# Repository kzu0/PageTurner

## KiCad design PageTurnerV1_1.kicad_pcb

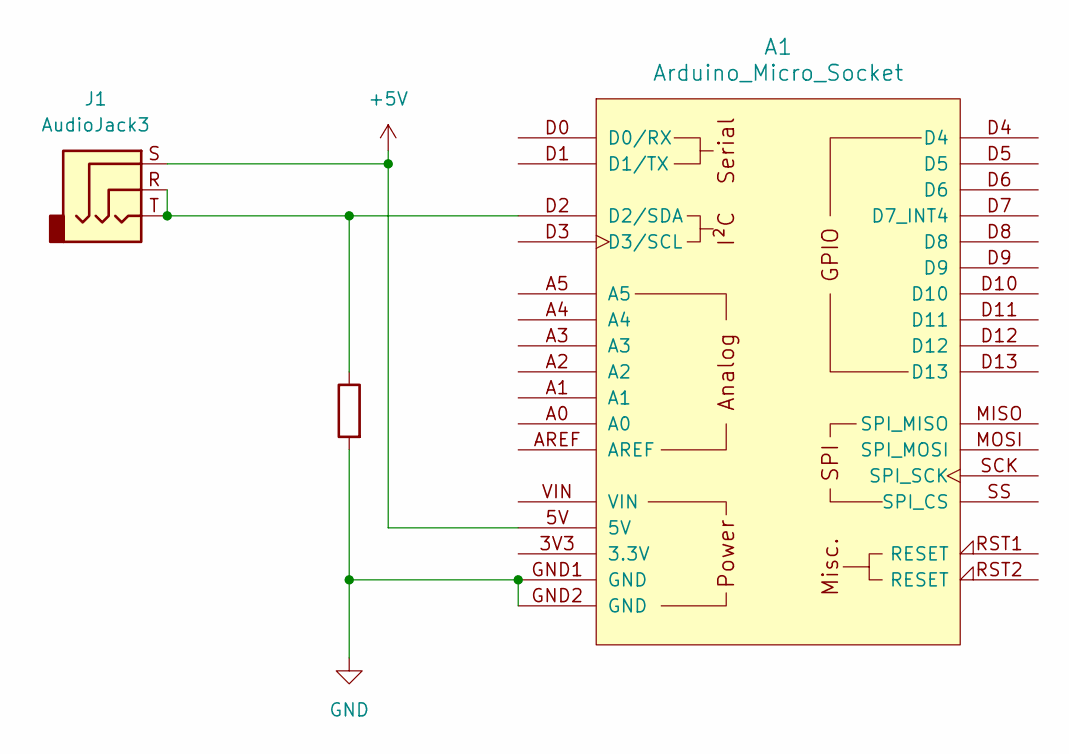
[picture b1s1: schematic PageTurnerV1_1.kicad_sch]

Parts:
A1: Arduino_Micro_Socket
J1: AudioJack3; Jack_TRS_6.3_Ketron
R1: R; R_Axial_DIN0207_L6.3mm_D2.5mm_P10.16mm_Horizontal

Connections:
+5V: A1.5V, J1.S
GND: A1.GND1 (GND), A1.GND2 (GND), R1.2
unnamed: A1.D2 (D2/SDA), J1.R, J1.T, R1.1

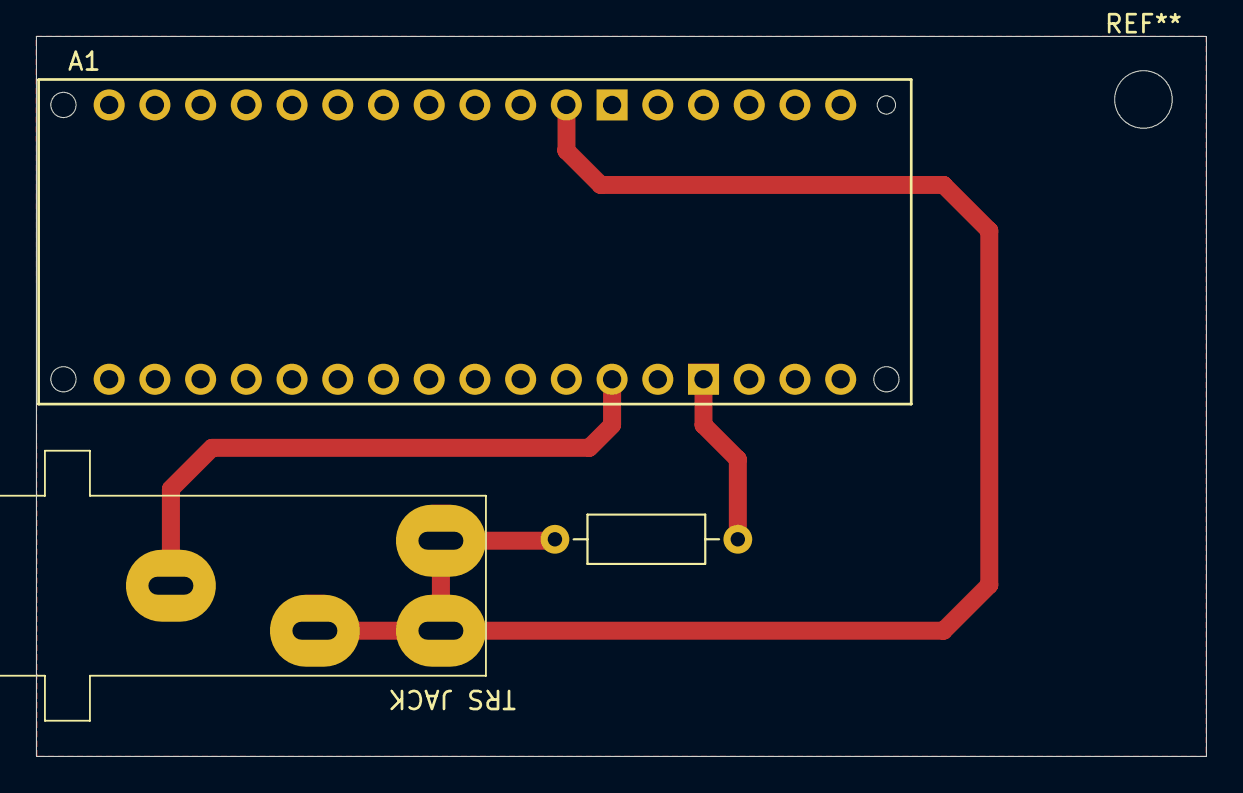
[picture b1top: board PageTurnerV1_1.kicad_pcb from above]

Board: 2 copper layers, 65.0 x 40.0 mm, 3 parts (0 on the bottom side), 3 nets.
